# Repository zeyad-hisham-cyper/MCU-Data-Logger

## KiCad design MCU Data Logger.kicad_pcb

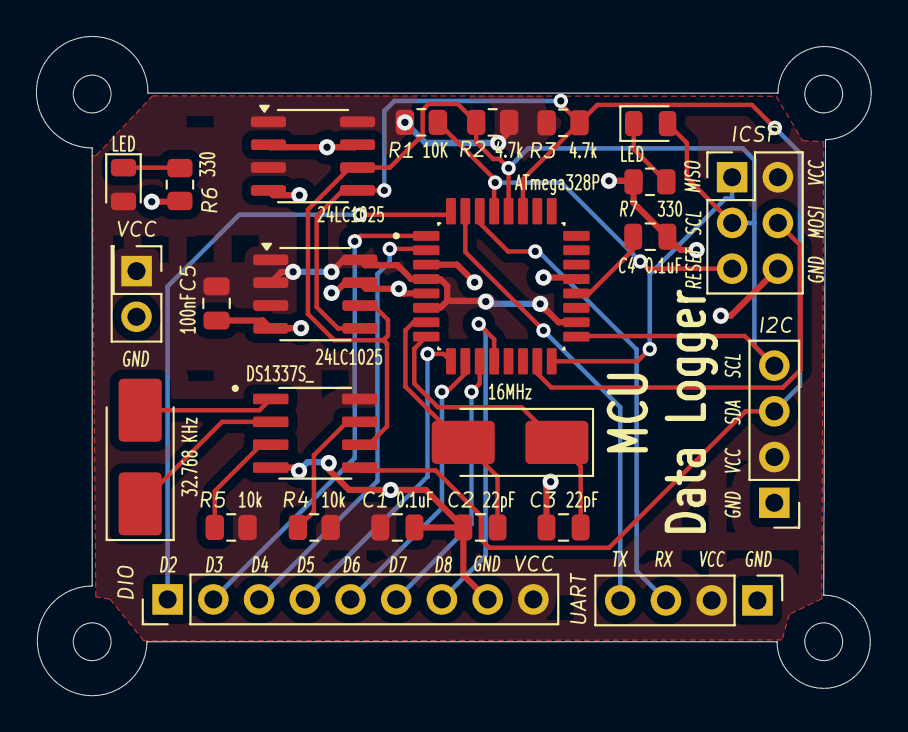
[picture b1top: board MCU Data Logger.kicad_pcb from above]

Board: 2 copper layers, 46.4 x 36.6 mm, 29 parts (0 on the bottom side), 25 nets.

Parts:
C1, C4: 0.1uF; C_0805_2012Metric
C2, C3: 22pF; C_0805_2012Metric
C5: 100nF; C_0805_2012Metric
D1, D2: LED; LED_0805_2012Metric
DIO: Conn_01x09_Pin; PinHeader_1x09_P2.54mm_Vertical
H1, H2, H3, H4: MountingHole; MountingHole_2.1mm
I2C: Conn_01x04_Pin; PinHeader_1x04_P2.54mm_Vertical
ICSP: Conn_02x03_Odd_Even; PinHeader_2x03_P2.54mm_Vertical
R1: 10K; R_0805_2012Metric
R2, R3: 4.7k; R_0805_2012Metric
R4, R5: 10k; R_0805_2012Metric
R6, R7: 330; R_0805_2012Metric
U1, U2: 24LC1025; SOIC-8_3.9x4.9mm_P1.27mm
U3: ATmega328P; QFP80P900X900X120-32N
U4: DS1337S_; SOIC127P600X175-8N
UART: Conn_01x04_Pin; PinHeader_1x04_P2.54mm_Vertical
VCC: Battery; PinHeader_2x01_P2.54mm_Vertical
Y1: 16MHz; Crystal_SMD_5032-2Pin_5.0x3.2mm_HandSoldering
Y2: 32.768 KHz; Crystal_SMD_5032-2Pin_5.0x3.2mm_HandSoldering

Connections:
/D2: DIO.1, U3.32 (PD2)
/D3: DIO.2, U3.1 (PD3)
/D4: DIO.3, U3.2 (PD4)
/D5: DIO.4, U3.9 (PD5)
/D6: DIO.5, U3.10 (PD6)
/D7: DIO.6, U3.11 (PD7)
/D8: DIO.7, U3.12 (PB0)
/MISO: ICSP.1, U3.16 (PB4)
/MOSI: ICSP.4, U3.15 (PB3)
/RESET: ICSP.5, R1.2, U3.29 (~RESET/PC6)
/RX: U3.30 (PD0), UART.3
/SCL: D1.2 (A), I2C.4, ICSP.3, R2.2, U1.6 (SCL), U2.6 (SCL), U3.17 (PB5), U3.28 (PC5), U4.6 (SCL)
/SDA: I2C.3, R3.2, U1.5 (SDA), U2.5 (SDA), U3.27 (PC4), U4.5 (SDA)
/TX: U3.31 (PD1), UART.4
/VCC: C1.2, C5.1, D2.2 (A), DIO.9, I2C.2, ICSP.2, R1.1, R2.1, R3.1, R4.1, R5.1, U1.1 (A0), U1.2 (A1), U1.3 (A2), U1.8 (VCC), U2.1 (A0), U2.3 (A2), U2.8 (VCC), U3.4 (VCC), U3.6 (VCC), U3.18 (AVCC), U4.8 (VCC), UART.2, VCC.1 (+)
GND: C1.1, C2.1, C3.1, C4.2, C5.2, DIO.8, I2C.1, ICSP.6, R6.1, R7.1, U1.4 (GND), U1.7 (WP), U2.2 (A1), U2.4 (GND), U2.7 (WP), U3.3 (GND), U3.5 (GND), U3.21 (GND), U4.4 (GND), UART.1, VCC.2 (-)
unnamed: D1.1 (K), R7.2
unnamed: D2.1 (K), R6.2
unnamed: C4.1, U3.20 (AREF)
unnamed: C2.2, U3.7 (XTAL1/PB6), Y1.2
unnamed: C3.2, U3.8 (XTAL2/PB7), Y1.1
unnamed: R4.2, U4.7 (SQW/~INT)
unnamed: U4.1 (X1), Y2.2
unnamed: U4.2 (X2), Y2.1
unnamed: R5.2, U4.3 (~INTA)

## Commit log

2025-08-24 Schematic Setup
2025-08-24 Adding all Schematic Element
2025-08-24 Editing some footprints
2025-08-28 Finishing Wiring
2025-08-28 Finishing Schematic
2025-08-28 Adding 3D Models and Starting Layout
2025-08-29 Components find there home
2025-09-02 adding outline
2025-09-04 2Layer Layout
2025-09-04 Finishing the 2Layer Version
2025-09-04 Completed 2layer board design
2025-09-04 Completing 2layer Board Design
